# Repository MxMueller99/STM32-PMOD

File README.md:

# STM32-PMOD
A compact and cheap PMOD compatible **STM32G030K8T6** based PCB. 

# Demo

# Features
- Arm Cortex-M0+ MCU, 64 MHz CPU, 64 KB Flash, 8 KB RAM
- STM32 USART1 TX/RX routed to the PMOD connector (Pin 2 & 3)
- Two onboard programmable LEDs
- I2C interface pins (For displays or sensors)
- SWD Interface for debugging/flashing the STM32 

# Hardware Overview

## Schematic

## Layout

## 3D Render

# Example - UART Blink

A small example to demonstrate the UART capabilities between the Arty Z7-20 Zynq PS and the STM32G030 MCU located under: `/UART_Blink_Example/`

- FPGA: Sends a UART message periodically to the STM32
- STM32: Receives the UART message and toggles the LED
    - "LED1" blinks when receiving UART messages from the FPGA
    - "LED2" blinks as a heartbeat of the STM32

## Setup
1. Connect the PMOD board to the FPGA
2. Flash the STM32 example via the SWD pins
3. Program the FPGA and run the example in Vitis

The FPGA needs to have the UART enabled and the uart_tx pin routed to the PMOD connector pin 3.

# Example - UART OLED

Another example to display incoming UART messages from the FPGA to a small OLED display connected to the PMOD board.

## Setup
Same as UART Blink

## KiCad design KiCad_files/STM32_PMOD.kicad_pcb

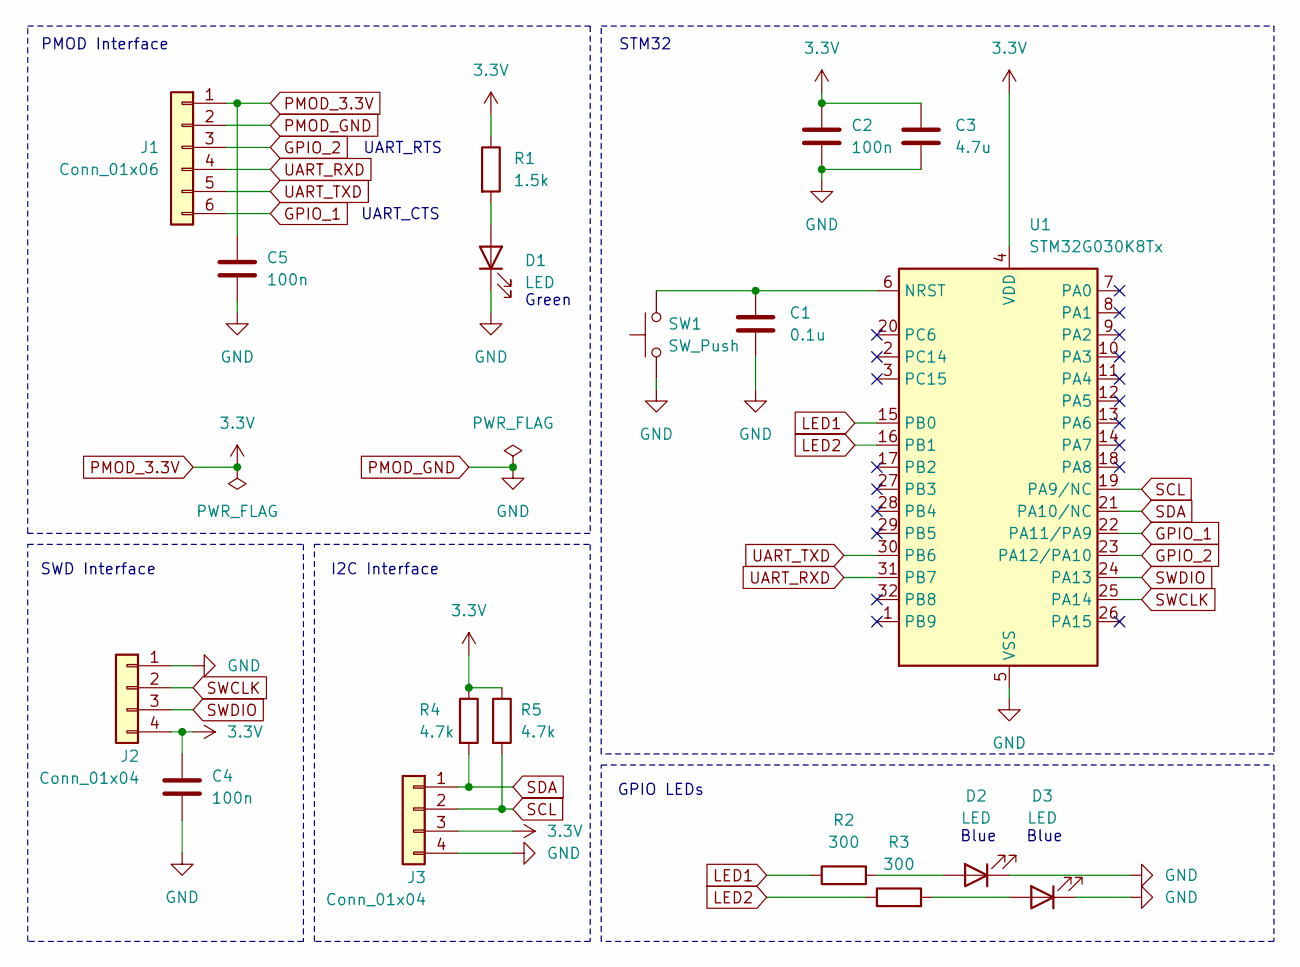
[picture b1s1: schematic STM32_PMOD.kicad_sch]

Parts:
C1: 0.1u; C_0402_1005Metric
C2, C4, C5: 100n; C_0402_1005Metric
C3: 4.7u; C_0805_2012Metric
D1, D2, D3: LED; LED_0603_1608Metric
J1: Conn_01x06; PinHeader_1x06_P2.54mm_Horizontal
J2: Conn_01x04; PinHeader_1x04_P2.54mm_Horizontal
J3: Conn_01x04; PinSocket_1x04_P2.54mm_Vertical
R1: 1.5k; R_0603_1608Metric
R2, R3: 300; R_0603_1608Metric
R4, R5: 4.7k; R_0603_1608Metric
SW1: SW_Push; SW_Tactile_SPST_NO_Straight_CK_PTS636Sx25SMTRLFS
U1: STM32G030K8Tx; LQFP-32_7x7mm_P0.8mm

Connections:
GPIO_1: J1.6, U1.22 (PA11/PA9)
GPIO_2: J1.3, U1.23 (PA12/PA10)
LED1: R2.1, U1.15 (PB0)
LED2: R3.1, U1.16 (PB1)
unnamed: D1.2 (A), R1.2
unnamed: D2.2 (A), R2.2
unnamed: D3.2 (A), R3.2
unnamed: C1.1, SW1.2, U1.6 (NRST)
PMOD_3.3V: C2.1, C3.1, C4.1, C5.1, J1.1, J2.4, J3.3, R1.1, R4.1, R5.1, U1.4 (VDD)
PMOD_GND: C1.2, C2.2, C3.2, C4.2, C5.2, D1.1 (K), D2.1 (K), D3.1 (K), J1.2, J2.1, J3.4, SW1.1, U1.5 (VSS)
SCL: J3.2, R5.2, U1.19 (PA9/NC)
SDA: J3.1, R4.2, U1.21 (PA10/NC)
SWCLK: J2.2, U1.25 (PA14)
SWDIO: J2.3, U1.24 (PA13)
UART_RXD: J1.4, U1.31 (PB7)
UART_TXD: J1.5, U1.30 (PB6)

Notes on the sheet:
GPIO LEDs
UART_RTS
PMOD Interface
Blue
UART_CTS
STM32
SWD Interface
Green
I2C Interface

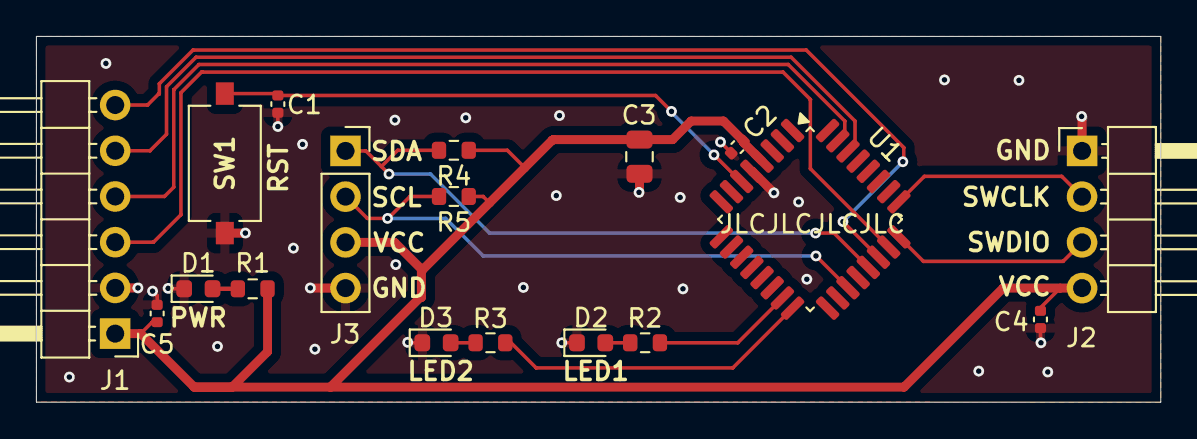
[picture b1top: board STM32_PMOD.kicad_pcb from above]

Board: 2 copper layers, 62.5 x 20.3 mm, 18 parts (0 on the bottom side), 16 nets.

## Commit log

2025-07-14 Commit with UART Blink Example
2025-07-23 Added OLED Display Example
